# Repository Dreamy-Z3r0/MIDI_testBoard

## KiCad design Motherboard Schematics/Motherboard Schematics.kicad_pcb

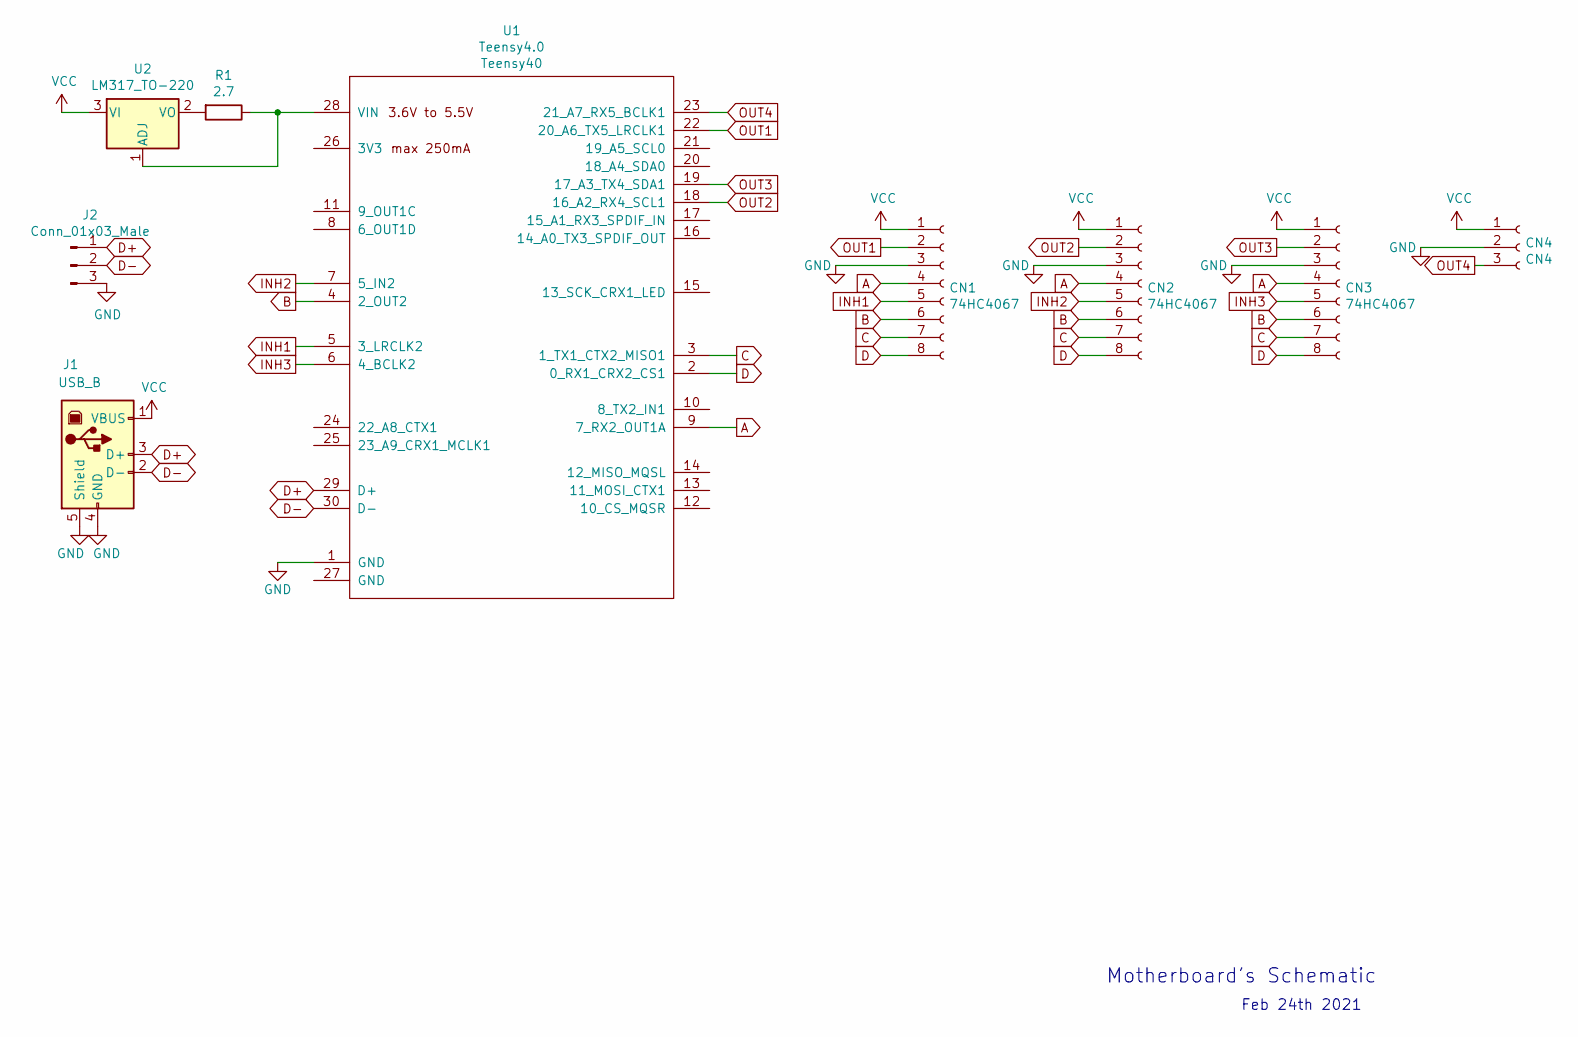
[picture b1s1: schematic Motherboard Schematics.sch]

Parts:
CN1, CN2, CN3: 74HC4067; PinSocket_1x08_P2.54mm_Vertical
CN4: CN4; PinSocket_1x03_P2.54mm_Vertical
J1: USB_B; USB_B_OST_USB-B1HSxx_Horizontal
J2: Conn_01x03_Male; PinSocket_1x03_P2.54mm_Vertical
R1: 2.7; R_Axial_DIN0207_L6.3mm_D2.5mm_P10.16mm_Horizontal
U1: Teensy4.0; Teensy40
U2: LM317_TO-220; TO-220-3_Vertical

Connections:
A: CN1.4, CN2.4, CN3.4, U1.9 (7_RX2_OUT1A)
B: CN1.6, CN2.6, CN3.6, U1.4 (2_OUT2)
C: CN1.7, CN2.7, CN3.7, U1.3 (1_TX1_CTX2_MISO1)
D: CN1.8, CN2.8, CN3.8, U1.2 (0_RX1_CRX2_CS1)
D+: J1.3 (D+), J2.1, U1.29 (D+)
D-: J1.2 (D-), J2.2, U1.30 (D-)
Earth: CN1.3, CN2.3, CN3.3, CN4.2, J1.4 (GND), J1.5 (Shield), J2.3, U1.1 (GND)
INH1: CN1.5, U1.5 (3_LRCLK2)
INH2: CN2.5, U1.7 (5_IN2)
INH3: CN3.5, U1.6 (4_BCLK2)
unnamed: R1.1, U1.28 (VIN), U2.1 (ADJ)
unnamed: R1.2, U2.2 (VO)
OUT1: CN1.2, U1.22 (20_A6_TX5_LRCLK1)
OUT2: CN2.2, U1.18 (16_A2_RX4_SCL1)
OUT3: CN3.2, U1.19 (17_A3_TX4_SDA1)
OUT4: CN4.3, U1.23 (21_A7_RX5_BCLK1)
VCC: CN1.1, CN2.1, CN3.1, CN4.1, J1.1 (VBUS), U2.3 (VI)

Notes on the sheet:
Motherboard's Schematic
Feb 24th 2021

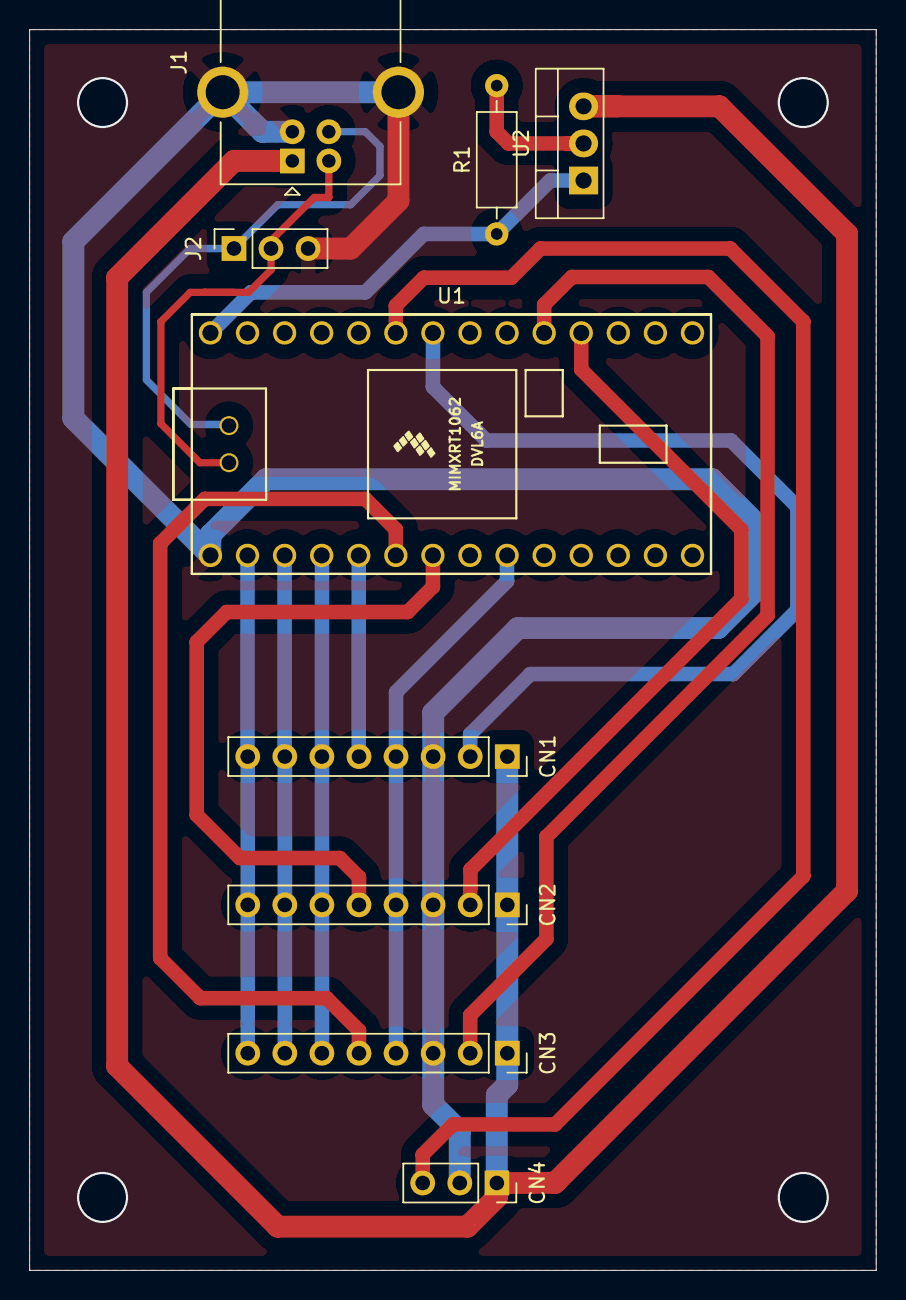
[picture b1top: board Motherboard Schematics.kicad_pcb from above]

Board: 2 copper layers, 58.0 x 85.0 mm, 9 parts (0 on the bottom side), 17 nets.

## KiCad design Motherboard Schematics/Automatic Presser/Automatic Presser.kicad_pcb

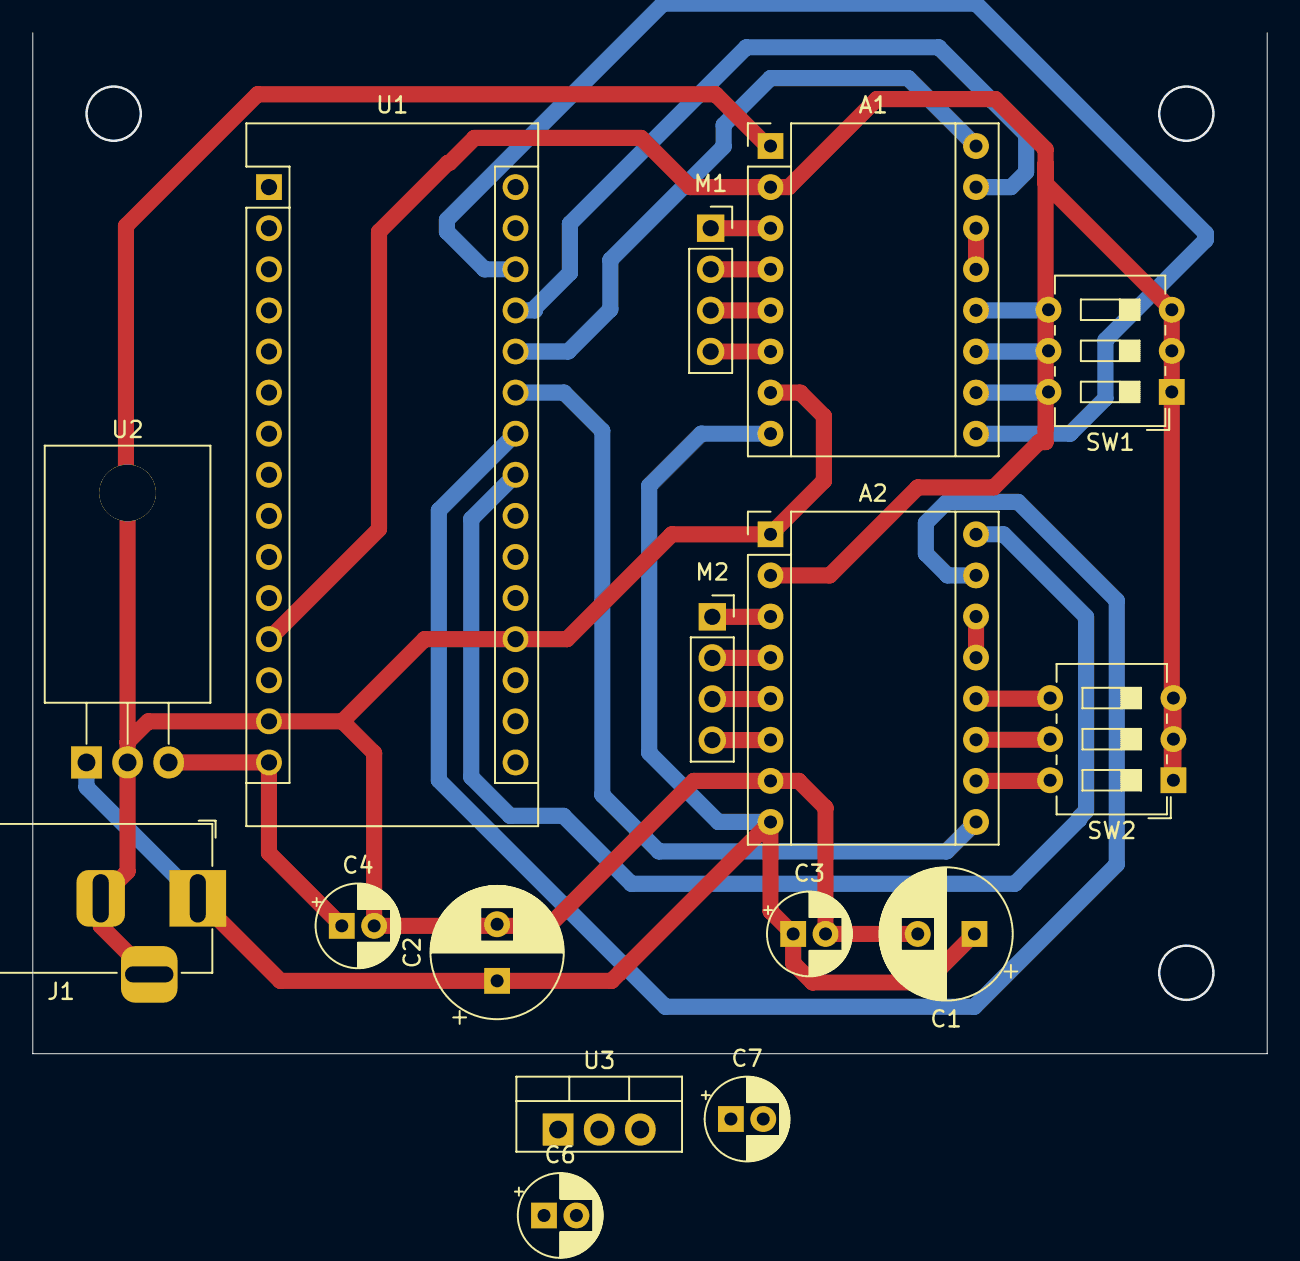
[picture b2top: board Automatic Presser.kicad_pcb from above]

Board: 2 copper layers, 76.3 x 63.1 mm, 16 parts (0 on the bottom side), 27 nets.

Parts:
A1, A2: Pololu_Breakout_A4988; Pololu_Breakout-16_15.2x20.3mm
C1, C2: 100uF; CP_Radial_D8.0mm_P3.50mm
C3, C6: 0.33uF; CP_Radial_D5.0mm_P2.00mm
C4, C7: 0.1uF; CP_Radial_D5.0mm_P2.00mm
J1: Barrel_Jack_Switch; BarrelJack_Horizontal
M1, M2: Stepper_Motor_bipolar; PinSocket_1x04_P2.54mm_Vertical
SW1, SW2: SW_DIP_x03; SW_DIP_SPSTx03_Slide_6.7x9.18mm_W7.62mm_P2.54mm_LowProfile
U1: Arduino_Nano_R3; Arduino_Nano
U2: LM7809_TO220; TO-220-3_Horizontal_TabDown
U3: LM7805_TO220; TO-220-3_Vertical

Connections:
+5VL: A1.2, A2.2, SW1.1, SW1.2, SW1.3, SW2.1, SW2.2, SW2.3, U1.12
+5VP: C7.1, U3.3
+9V: C4.1, C6.1, U1.15, U2.3, U3.1
+12V: A1.8, A2.8, C1.1, C2.1, C3.1, J1.1, U2.1
A1_DIR: A1.16, U1.26
A1_EN: A1.9, U1.28
A1_STEP: A1.15, U1.27
A2_DIR: A2.16, U1.23
A2_EN: A2.9, U1.25
A2_STEP: A2.15, U1.24
GND: A1.1, A1.7, A2.1, A2.7, C1.2, C2.2, C3.2, C4.2, C6.2, C7.2, J1.2, J1.3, U1.14, U1.19, U2.2, U3.2
unnamed: A1.10, SW1.6
unnamed: A1.11, SW1.5
unnamed: A1.12, SW1.4
unnamed: A1.13, A1.14
unnamed: A2.10, SW2.6
unnamed: A2.11, SW2.5
unnamed: A2.12, SW2.4
unnamed: A2.13, A2.14
S11A: A1.4, M1.2
S11B: A1.3, M1.1
S12A: A1.5, M1.3
S12B: A1.6, M1.4
S21A: A2.4, M2.2
S21B: A2.3, M2.1
S22A: A2.5, M2.3
S22B: A2.6, M2.4

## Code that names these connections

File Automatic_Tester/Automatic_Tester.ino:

#define A2_DIR  PD5
#define A2_STEP PD6
#define A2_EN   PD7
#define A1_DIR  PB0
#define A1_STEP PB1
#define A1_EN   PB2

#define A1_STEP_HIGH  PORTB |=  (1<< A1_STEP) 
#define A1_STEP_LOW   PORTB &= ~(1<< A1_STEP)

#define A2_STEP_HIGH  PORTD |= (1<< A2_STEP)
#define A2_STEP_HIGH  PORTD &= ~(1<< A2_STEP)

uint8_t startButton = D3; /& use INT1
bool running = false;
float lastPos[2] = {1,1};

void setup()
{
    DDRD &= ~(1<< startButton);
    // Rising edge of INT1 generates interrupt
    EICRA |= (1<<ISC11);
    EICRA |= (1<<ISC10;
    // Enable interrrupts for INT1
    EIMSK |= (1<< INT1); 
    
    get_lastPosition();
    moveTo(0,0, lastPos[0], lastPos[2]);
}

void loop()
{
  if(running)
  {
    running = false;
    run();
    attachInterrupt(digitalPinToInterrupt(startButton),startService,RISING);
  }
}
ISR(INT1_vect)
{
  detachInterrupt(digitalPinToInterrupt(startButton));
  running = true;
}

void run()
{
  
}

void moveTo(float des_X1, float des_Y1, float from_X0, float from_Y0)
{
  lastPos[0] = des_X1;
  lastPos[1] = des_Y1;
}

void get_lastPosition()
{
  
}

void save_lastPosition()
{
  
}

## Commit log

2021-03-19 Create firmware file
2021-03-19 KiCAD files
2021-04-08 addition to code
2021-04-08 copy from referrence
    check check
2021-04-10 Change in IDE
2021-04-10 Create timer control routines
2021-04-10 Resolve a minor mistake: One missing character
2021-04-10 Add some comments
2021-04-10 Update timer 1 ISR: Stepper motors' operations.
2021-04-10 Additional features for managing PWM duty cycle
2021-04-10 Add variables storing PWM information for stepper motors
2021-04-11 Add some formatting
2021-04-12 Add control methods for START button. Add functions for cursor movements.
2021-04-12 Add features for enabling or disabling motors. Make some variables friendlier to read.
2021-04-13 Add some comments.
2021-04-13 Changes to schematics
2021-04-13 Update pin declarations based on changes in schematics.
2021-04-13 Add STOP commands.
2021-04-13 Re-arrange STOP command's routines. Add solutions for overflowed timer counter(s).
2021-04-13 Add cursor-moving routine following START command.
2021-04-15 Add simulations
2021-04-18 Change PWM method; Add debugging method using Serial; Fix existing errors.
    1. Removed inverting fast PWM mode from Timer 1. Timer 1 now operates in normal mode; Pseudo-PWM signals to control stepper motors are generated by outputting HIGH/LOW on the chosen pins.
    2. Outputting on Serial Monitor is now used in order for user to observe the behaviours of some important variables.
    3. Inputting method of push button is currently not operational. Therefore, commands 'Y' (START) and 'N' (STOP) from Serial Monitor are now temporary solution.
    4. Some variables' names have been changed for more professional appearance.
    5. System's behaviour has been adjusted when the START command is initiated.
    6. A f
2021-04-20 Make the control more detailed and universal.
    1. Some variables' names have been changed to indicate the targets of usage (Stepper motors).
    2. The port pins that are used for controlling stepper motors could now be easily changed using macros at the beginning of the code. Current port in use for controlling stepper motors is ATmega328P's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
2021-04-20 Specify some current Arduino pin names.
2021-04-20 Use Timer2 to control stepper motors; Preserve 16-bit Timer 1 for servo motor.
2021-04-20 Add configurations for servo controlling feature.
2021-04-20 Erg... Nada.
2021-04-21 Resolve some issues related to the theories of Timer PWM.
2021-05-20 Nada
2021-05-20 Git test
2021-05-21 Tests for servo motor
2021-05-21 Combined test for Servo and stepper motors.
2021-05-21 Update Stop routine
2021-05-21 Remove excessive lines
2021-05-22 Fix the issue of excessive steps.
2021-06-27 Modify stepper motor behaviour.
